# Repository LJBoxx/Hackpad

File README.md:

# PotatoPAD
My version of the Hackpad ^w^

well now its **POTATOPAD**
## Hardware ! 
Here is a (bad) screenshot of the schematic :

And another (bad) screenshot of the pcb : 

And here is an overview with the case : 

Not to forget the kicad render ! 

## BOM
It will use : 
- 1x Seeed XIAO RP2040
- 1x 0.91 inch OLED display
- 12x 1N4148 Diodes
- 12x MX style switch
- 12x Blank DSA keycaps 
- 12x SK6812 MINI-E
- 2x 3d printed parts
- 3x M3x16mm screw
- 3x M3x5mx4mm heatset insert
OPTIONNAL
- 2x 6x6 spst push button i have some laying around so id figured might aswell use them :D
- 1x Li-ion battery that fits inside, if you want to use ble and zmk firmware. There is a pin header for this case. 
**DISCLAMER!! BE CAREFUL USING LI-ION BATTERY. I WILL NOT BE RESPONSIBLE FOR ANY DAMAGES THAT MAY OUTCOME FROM THIS HARDWARE**

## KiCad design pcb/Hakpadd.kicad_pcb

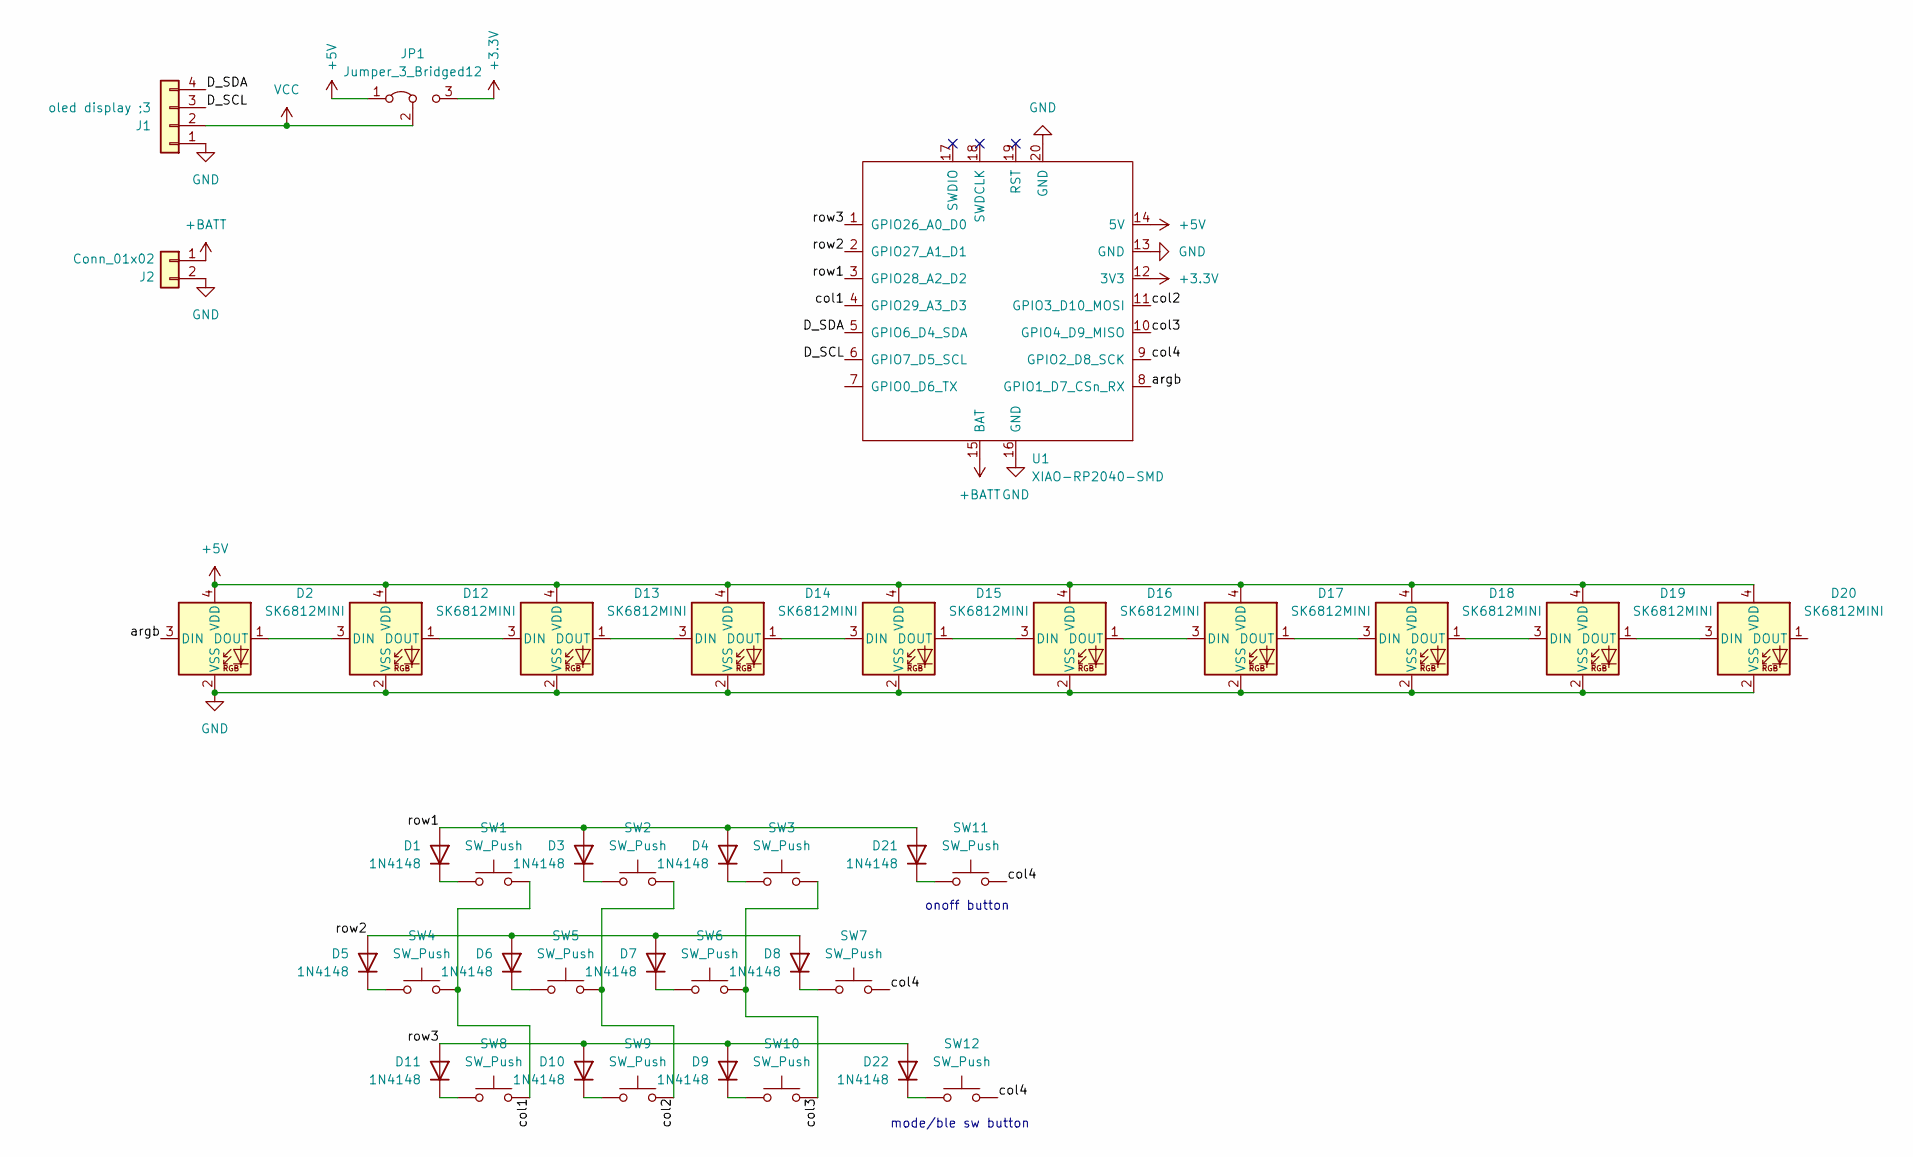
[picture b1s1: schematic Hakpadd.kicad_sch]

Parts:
D1, D3, D4, D5, D6, D7, D8, D9, D10, D11, D21, D22: 1N4148; D_DO-35_SOD27_P7.62mm_Horizontal
D2, D12, D13, D14, D15, D16, D17, D18, D19, D20: SK6812MINI; MX_SK6812MINI-E
J1: oled display ;3; SSD1306_OLED-0.91-128x32
J2: Conn_01x02; PinHeader_1x02_P2.54mm_Vertical
JP1: Jumper_3_Bridged12; SolderJumper-3_P1.3mm_Bridged2Bar12_Pad1.0x1.5mm
SW1, SW2, SW3, SW4, SW5, SW6, SW7, SW8, SW9, SW10: SW_Push; CherryMX_1.00u
SW11, SW12: SW_Push; SW_PUSH_6mm
U1: XIAO-RP2040-SMD

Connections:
+3.3V: JP1.3 (B), U1.12 (3V3)
+5V: D2.4 (VDD), D12.4 (VDD), D13.4 (VDD), D14.4 (VDD), D15.4 (VDD), D16.4 (VDD), D17.4 (VDD), D18.4 (VDD), D19.4 (VDD), D20.4 (VDD), JP1.1 (A), U1.14 (5V)
+BATT: J2.1, U1.15 (BAT)
/D_SCL: J1.3, U1.6 (GPIO7_D5_SCL)
/D_SDA: J1.4, U1.5 (GPIO6_D4_SDA)
/argb: D2.3 (DIN), U1.8 (GPIO1_D7_CSn_RX)
/col1: SW1.2, SW4.2, SW8.2, U1.4 (GPIO29_A3_D3)
/col2: SW2.2, SW5.2, SW9.2, U1.11 (GPIO3_D10_MOSI)
/col3: SW3.2, SW6.2, SW10.2, U1.10 (GPIO4_D9_MISO)
/col4: SW7.2, SW11.2, SW12.2, U1.9 (GPIO2_D8_SCK)
/row1: D1.2 (A), D3.2 (A), D4.2 (A), D21.2 (A), U1.3 (GPIO28_A2_D2)
/row2: D5.2 (A), D6.2 (A), D7.2 (A), D8.2 (A), U1.2 (GPIO27_A1_D1)
/row3: D9.2 (A), D10.2 (A), D11.2 (A), D22.2 (A), U1.1 (GPIO26_A0_D0)
GND: D2.2 (VSS), D12.2 (VSS), D13.2 (VSS), D14.2 (VSS), D15.2 (VSS), D16.2 (VSS), D17.2 (VSS), D18.2 (VSS), D19.2 (VSS), D20.2 (VSS), J1.1, J2.2, U1.13 (GND), U1.16 (GND), U1.20 (GND)
unnamed: D1.1 (K), SW1.1
unnamed: D3.1 (K), SW2.1
unnamed: D4.1 (K), SW3.1
unnamed: D5.1 (K), SW4.1
unnamed: D6.1 (K), SW5.1
unnamed: D7.1 (K), SW6.1
unnamed: D8.1 (K), SW7.1
unnamed: D9.1 (K), SW10.1
unnamed: D10.1 (K), SW9.1
unnamed: D11.1 (K), SW8.1
unnamed: D2.1 (DOUT), D12.3 (DIN)
unnamed: D12.1 (DOUT), D13.3 (DIN)
unnamed: D13.1 (DOUT), D14.3 (DIN)
unnamed: D14.1 (DOUT), D15.3 (DIN)
unnamed: D15.1 (DOUT), D16.3 (DIN)
unnamed: D16.1 (DOUT), D17.3 (DIN)
unnamed: D17.1 (DOUT), D18.3 (DIN)
unnamed: D18.1 (DOUT), D19.3 (DIN)
unnamed: D19.1 (DOUT), D20.3 (DIN)
unnamed: D21.1 (K), SW11.1
unnamed: D22.1 (K), SW12.1
VCC: J1.2, JP1.2 (C)

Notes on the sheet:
onoff button
mode/ble sw button

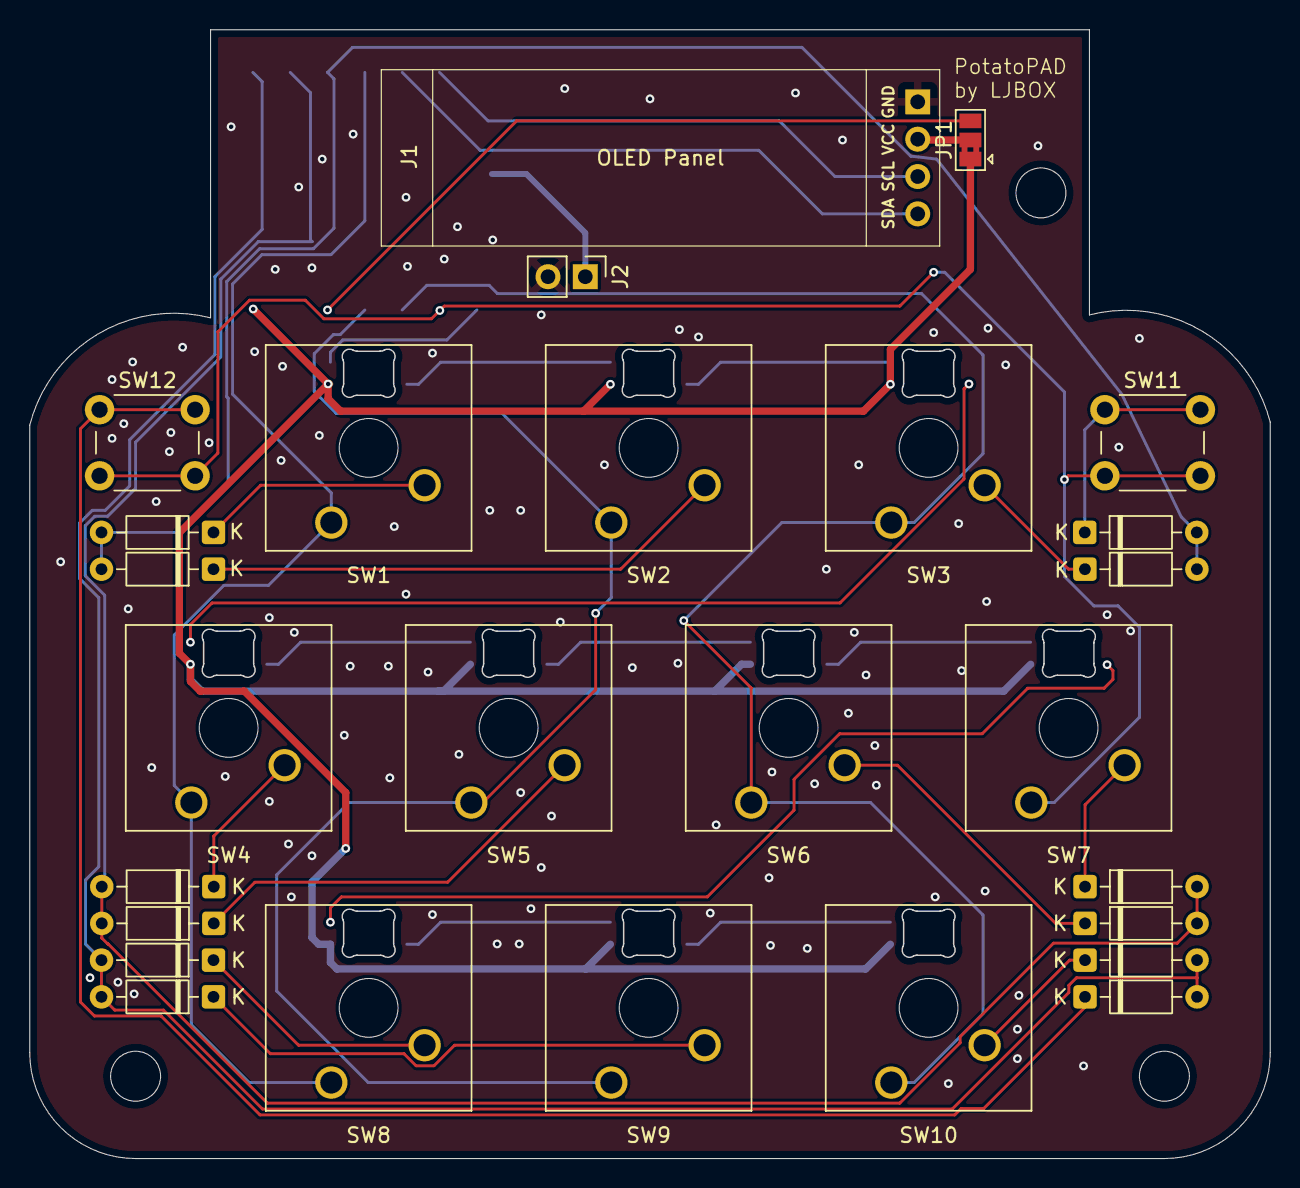
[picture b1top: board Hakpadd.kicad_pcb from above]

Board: 2 copper layers, 84.3 x 76.8 mm, 38 parts (1 on the bottom side), 36 nets.

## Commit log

2026-01-08 Update project name to POTATOPAD
2026-01-09 Push (well almost full project lol)
2026-01-09 Revise README for PotatoPAD project details
    Updated the README to reflect the new project name and added hardware and BOM sections with images and components.
2026-01-09 rename hakpad folder to pcb
2026-01-09 KMK fw added
    (yes its ai generatad i am lazy right now 😭 )
